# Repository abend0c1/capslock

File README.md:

USB dongle that lights up when the capslock light is on
=========

This is a USB capslock-light-on-a-stick that lights up when the
CapsLock LED would normally be lit. Some Lenovo laptops do not have
a CapsLock LED.

In addition, the SCROLL LOCK keystroke
is sent to the host every 60 seconds to prevent the host from
detecting a "time out" situation.

The SCROLL LOCK light, present on many older keyboards, will flash
to indicate the keystroke injection is active. The LED on this
device will also briefly blink for each keystroke injection.

Operation
-----
Plug it in (relaxen und watschen der blinkenlichten)

Prototype
-----

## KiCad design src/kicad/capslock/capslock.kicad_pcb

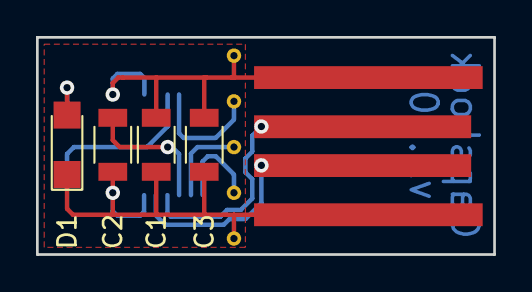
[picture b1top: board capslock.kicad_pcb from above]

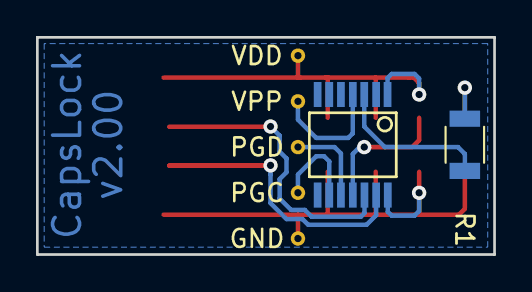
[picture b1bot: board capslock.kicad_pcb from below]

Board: 2 copper layers, 25.4 x 12.1 mm, 12 parts (7 on the bottom side), 10 nets.

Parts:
C1: 100nF; C_1206
C2: 470nF; C_1206
C3: 2.2μF; C_1206
D1: LED; LED_1206
GND: GND; 1pin
J1: USB_A; USB-SMT-plug
PGC: PGC; 1pin
PGD: PGD; 1pin
R1: 470Ω; R_1206
U1: PIC16(L)F1455-I/ST; SSOP-14
VDD: VDD; 1pin
VPP: VPP; 1pin

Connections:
/D+: J1.3, U1.13
/D-: J1.2, U1.12
/N1: D1.2, R1.2
/PGC: PGC.1, U1.9
/PGD: PGD.1, U1.10
/RA4: R1.1, U1.3
/VPP: U1.4, VPP.1
/VUSB: C2.1, U1.11
GND: C1.2, C2.2, C3.2, D1.1, GND.1, J1.4, U1.14
VDD: C1.1, C3.1, J1.1, U1.1, VDD.1

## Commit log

2016-11-04 Initial version
2016-11-04 Initial 1455 commit
2016-11-04 Saved 18k2550 project settings
2016-11-04 Added capslock.cfg
2016-11-04 Updated settings for USB FS + CPU 24MHz
2016-11-05 Moved button
2016-11-05 Added mcppi project file
2016-11-05 Doc update.
2016-11-06 Added code to support the button
2016-11-06 Ported logic from PIC18F25K50 version
2016-11-06 Updated USB HID report descriptor
2016-11-09 First working version
2017-09-09 Added mouse micro-movements
2017-10-22 First PCB-only version that plugs directly into a USB port
2017-11-02 Gerbers used for ALLPCB job 2C036588
2017-11-03 Removed button logic because the v2.00 PCB does not have a button
2017-12-17 Cosmetic fixes to USBdsc.c
2017-12-17 Removed micro mouse movements because Linux apparently does not send keyboard LED status updates unless the keyboard is a BOOT keyboard.
2017-12-17 Removed vestigal button logic
2017-12-17 Patched the comments after botching the merge
2017-12-17 Added image of capslock prototype
